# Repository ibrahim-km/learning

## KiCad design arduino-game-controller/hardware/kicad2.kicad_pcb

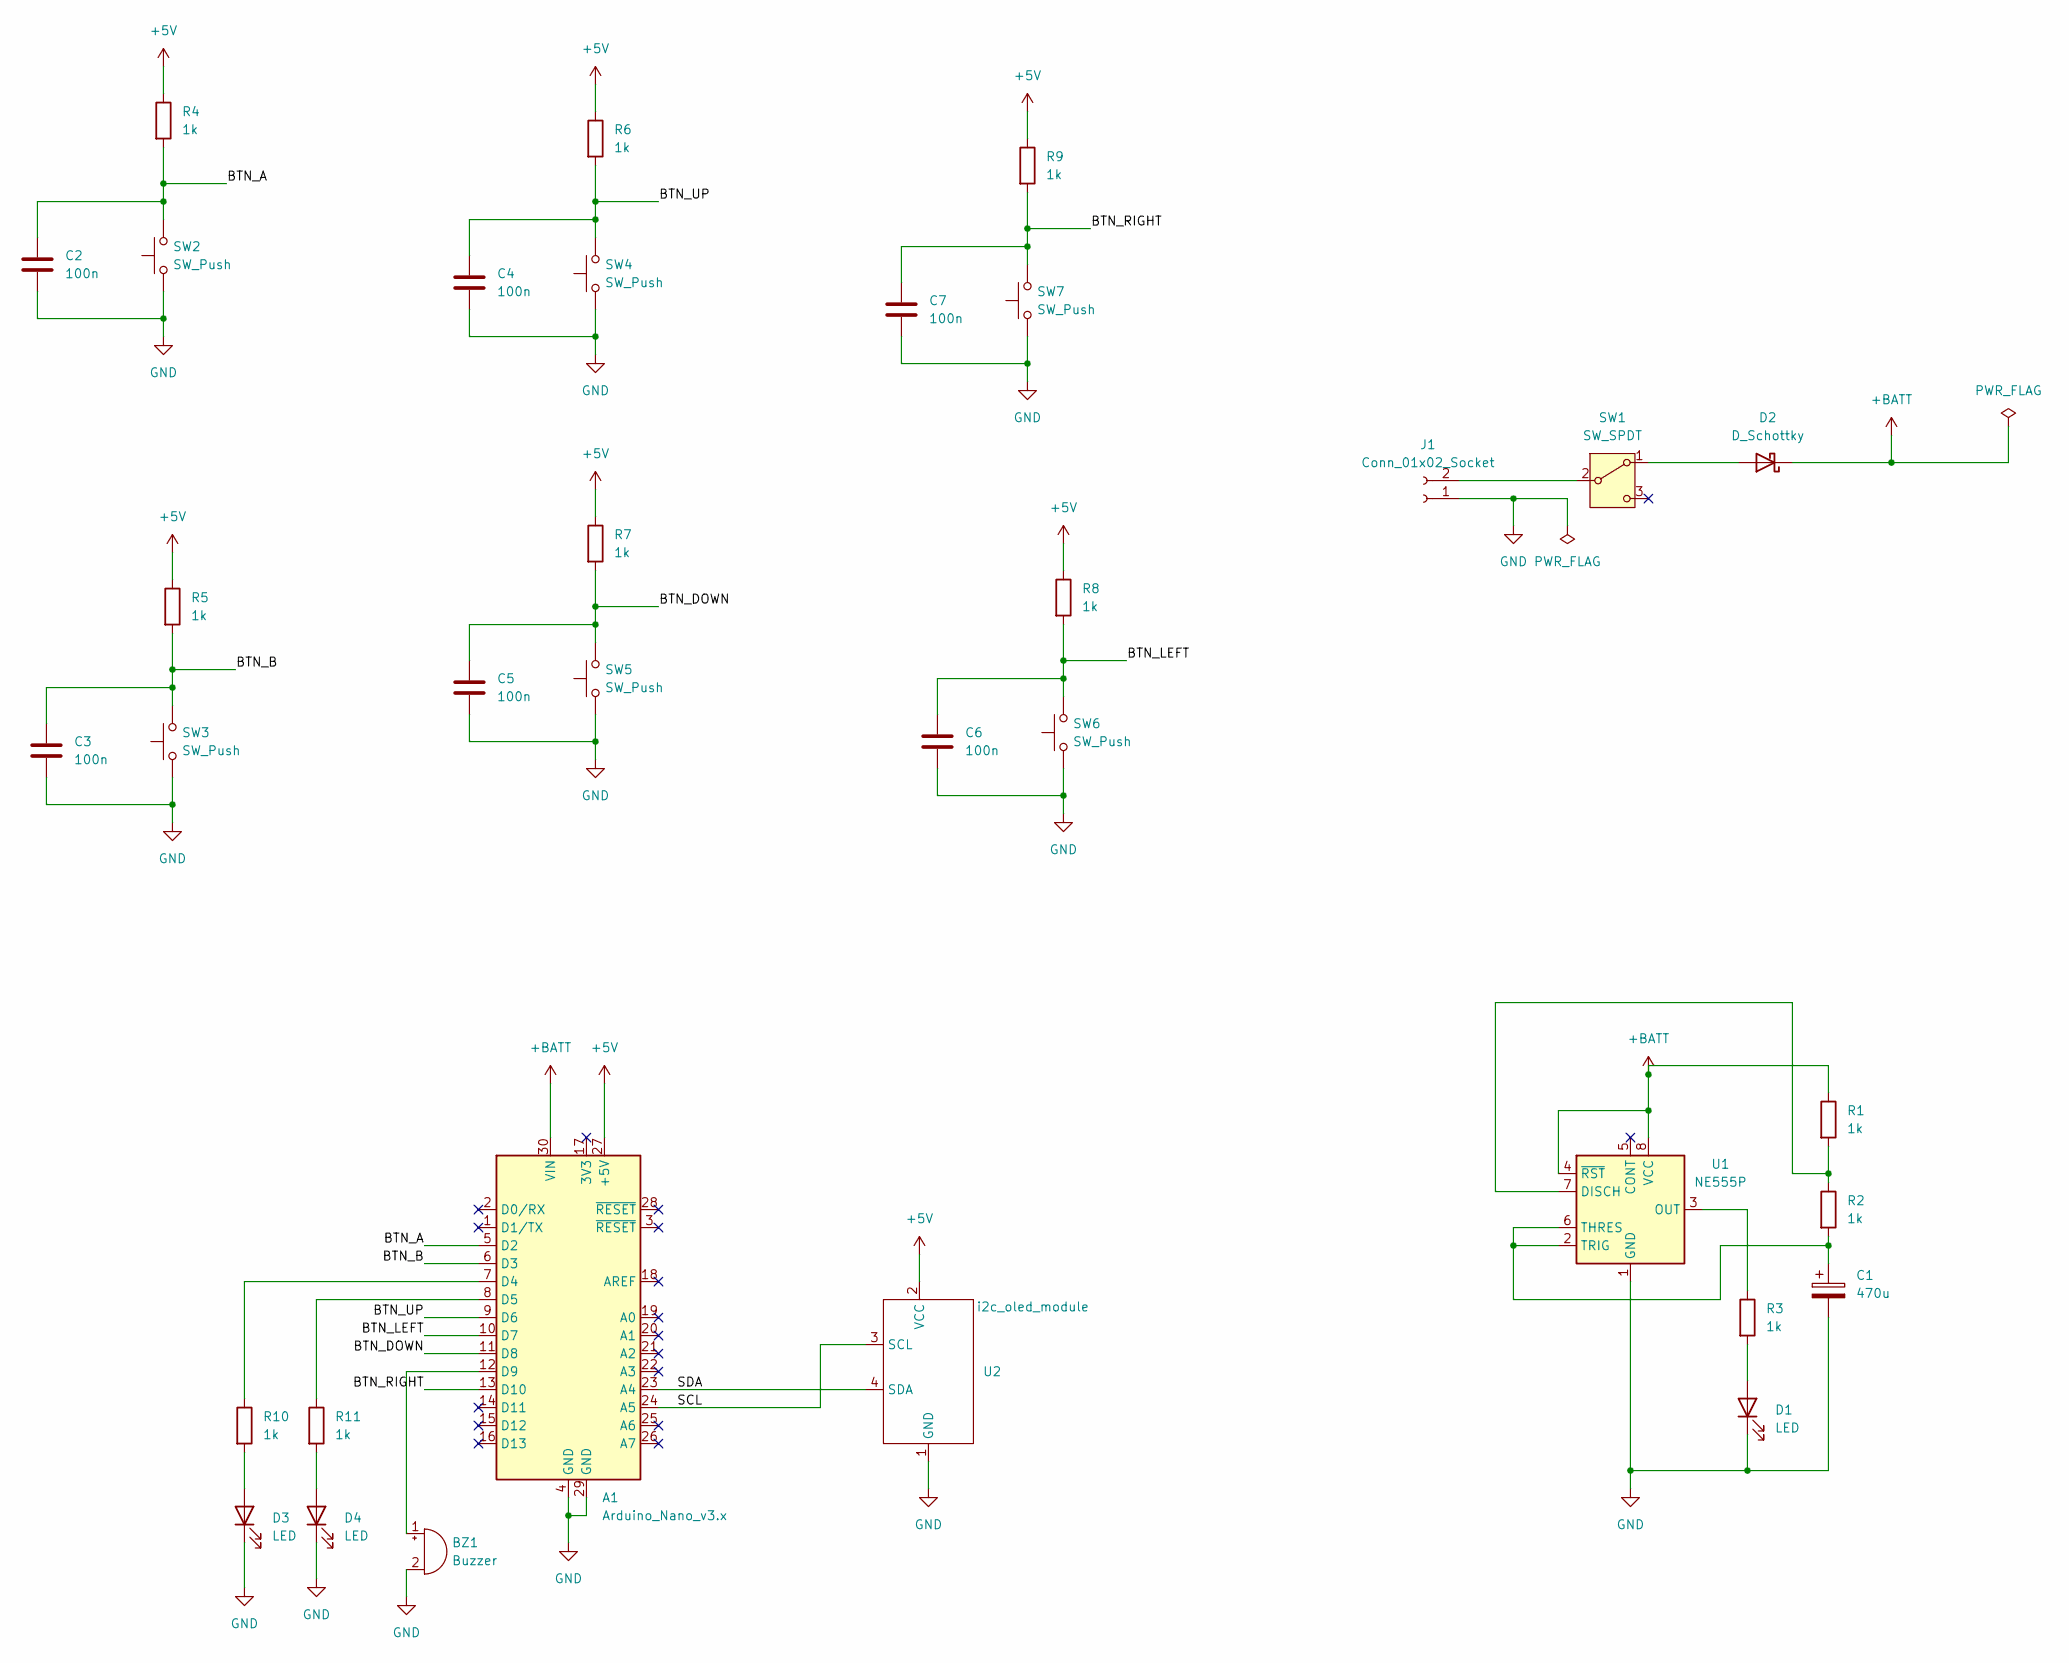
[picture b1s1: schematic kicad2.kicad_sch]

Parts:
A1: Arduino_Nano_v3.x; Arduino_Nano_WithMountingHoles
BZ1: Buzzer; Buzzer_12x9.5RM7.6
C1: 470u; CP_Radial_D8.0mm_P3.50mm
C2, C3, C4, C5, C6, C7: 100n; C_Disc_D5.0mm_W2.5mm_P5.00mm
D1, D3, D4: LED; LED_D5.0mm
D2: D_Schottky; D_DO-41_SOD81_P10.16mm_Horizontal
J1: Conn_01x02_Socket; PinHeader_1x02_P2.54mm_Vertical
R1, R2, R3, R4, R5, R6, R7, R8, R9, R10, R11: 1k; R_Axial_DIN0207_L6.3mm_D2.5mm_P10.16mm_Horizontal
SW1: SW_SPDT; PinHeader_1x03_P2.54mm_Vertical
SW2, SW3, SW4, SW5, SW6, SW7: SW_Push; SW_PUSH_6mm_H5mm
U1: NE555P; DIP-8_W7.62mm
U2: i2c_oled_module; PinHeader_1x04_P2.54mm_Vertical

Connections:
+5V: A1.27 (+5V), R4.1, R5.1, R6.1, R7.1, R8.1, R9.1, U2.2 (VCC)
+BATT: A1.30 (VIN), D2.1 (K), R1.1, U1.4 (~RST), U1.8 (VCC)
/BTN_A: A1.5 (D2), C2.1, R4.2, SW2.2
/BTN_B: A1.6 (D3), C3.1, R5.2, SW3.2
/BTN_DOWN: A1.11 (D8), C5.1, R7.2, SW5.2
/BTN_LEFT: A1.10 (D7), C6.1, R8.2, SW6.2
/BTN_RIGHT: A1.13 (D10), C7.1, R9.2, SW7.2
/BTN_UP: A1.9 (D6), C4.1, R6.2, SW4.2
/SCL: A1.24 (A5), U2.3 (SCL)
/SDA: A1.23 (A4), U2.4 (SDA)
GND: A1.4 (GND), A1.29 (GND), BZ1.2 (-), C1.2, C2.2, C3.2, C4.2, C5.2, C6.2, C7.2, D1.1 (K), D3.1 (K), D4.1 (K), J1.1, SW2.1, SW3.1, SW4.1, SW5.1, SW6.1, SW7.1, U1.1 (GND), U2.1 (GND)
unnamed: A1.7 (D4), R10.1
unnamed: A1.8 (D5), R11.1
unnamed: A1.12 (D9), BZ1.1 (+)
unnamed: D1.2 (A), R3.2
unnamed: D2.2 (A), SW1.1 (A)
unnamed: D3.2 (A), R10.2
unnamed: D4.2 (A), R11.2
unnamed: J1.2, SW1.2 (B)
unnamed: R1.2, R2.1, U1.7 (DISCH)
unnamed: R3.1, U1.3 (OUT)
unnamed: C1.1, R2.2, U1.2 (TRIG), U1.6 (THRES)

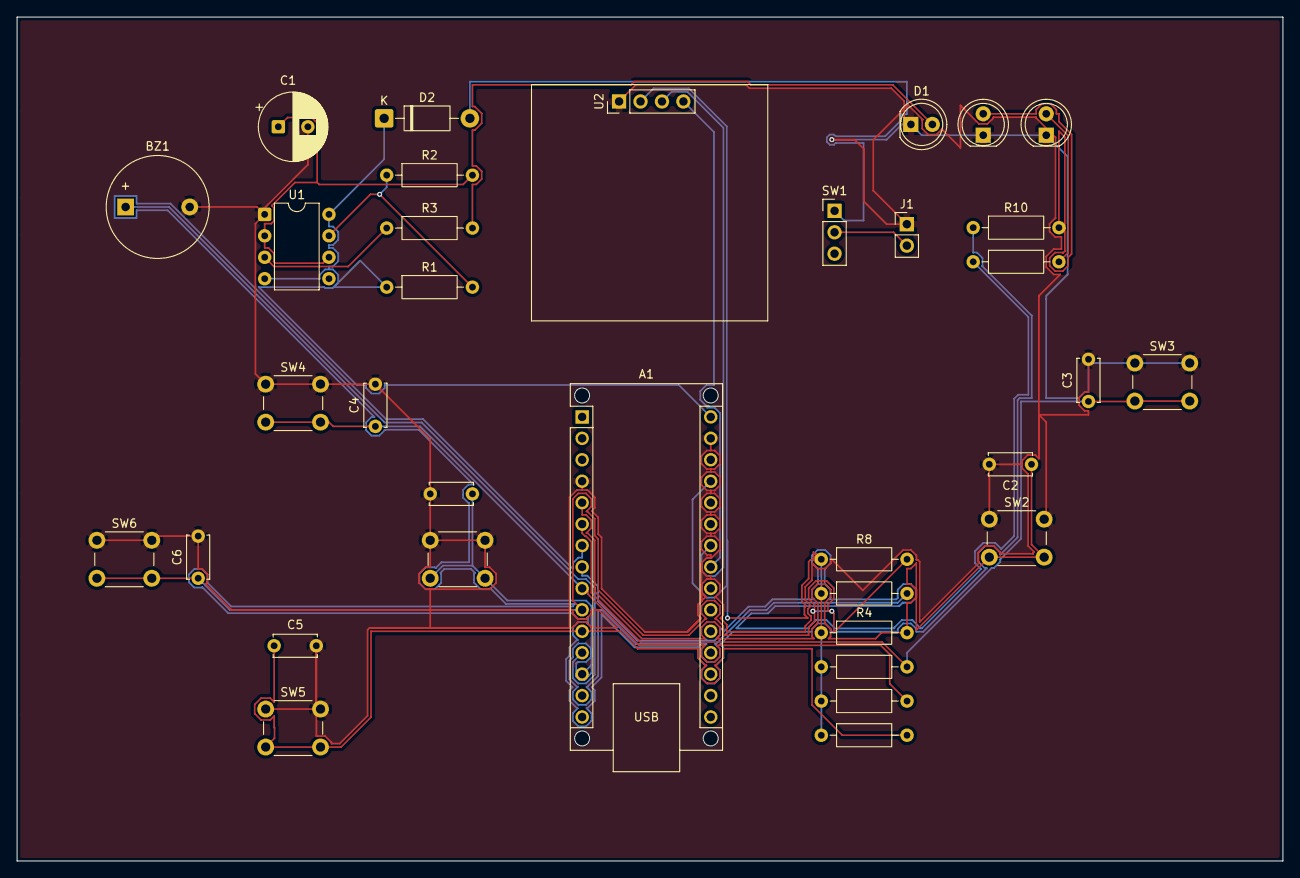
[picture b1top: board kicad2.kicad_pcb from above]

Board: 2 copper layers, 150.0 x 100.0 mm, 34 parts (0 on the bottom side), 22 nets.

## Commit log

2026-06-23 Create gamepad-pcb
2026-06-23 Create gamepad-pcb
2026-06-23 Rename gamepad-pcb to arduino-controller-basic
